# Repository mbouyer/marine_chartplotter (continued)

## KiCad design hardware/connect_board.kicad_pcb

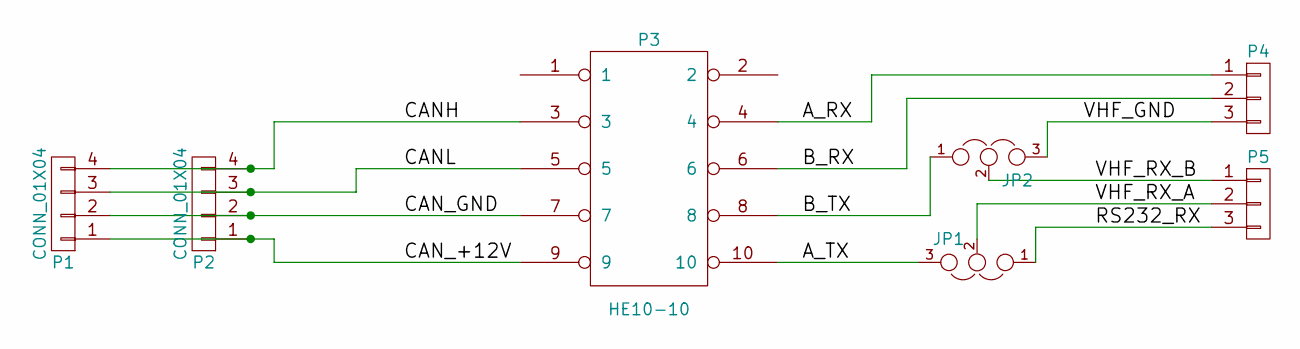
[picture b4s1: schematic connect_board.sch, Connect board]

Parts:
JP1, JP2: JUMPER3; Pin_Header_Straight_1x03
P1, P2: CONN_01X04; phoenix_1770979
P3: HE10-10; he10s-10d
P4, P5: CONN_01X03; TerminalBlock_Pheonix_MPT-2.54mm_3pol

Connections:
/A_RX: P3.4, P4.1
/A_TX: JP1.3, P3.10
/B_RX: P3.6, P4.2
/B_TX: JP2.1, P3.8
/CANH: P1.4, P2.4, P3.3
/CANL: P1.3, P2.3, P3.5
/CAN_+12V: P1.1, P2.1, P3.9
/CAN_GND: P1.2, P2.2, P3.7
/RS232_RX: JP1.1, P5.3
/VHF_GND: JP2.3, P4.3
/VHF_RX_A: JP1.2, P5.2
/VHF_RX_B: JP2.2, P5.1

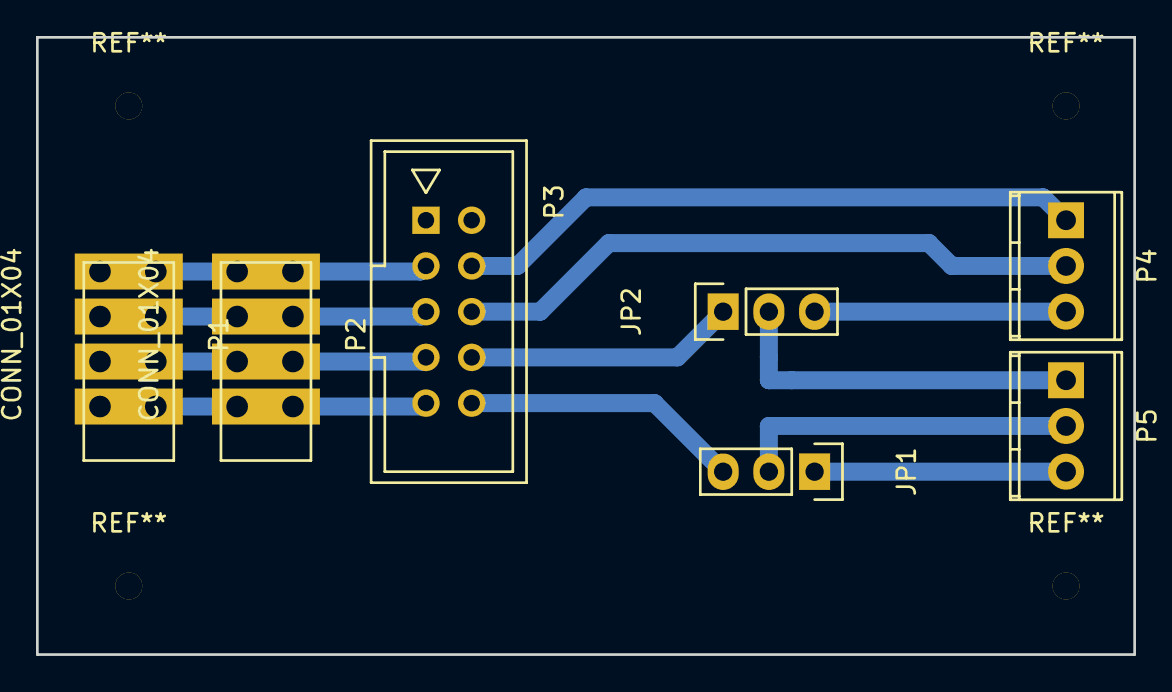
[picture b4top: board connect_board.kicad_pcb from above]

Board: 2 copper layers, 61.0 x 34.3 mm, 7 parts (0 on the bottom side), 12 nets.

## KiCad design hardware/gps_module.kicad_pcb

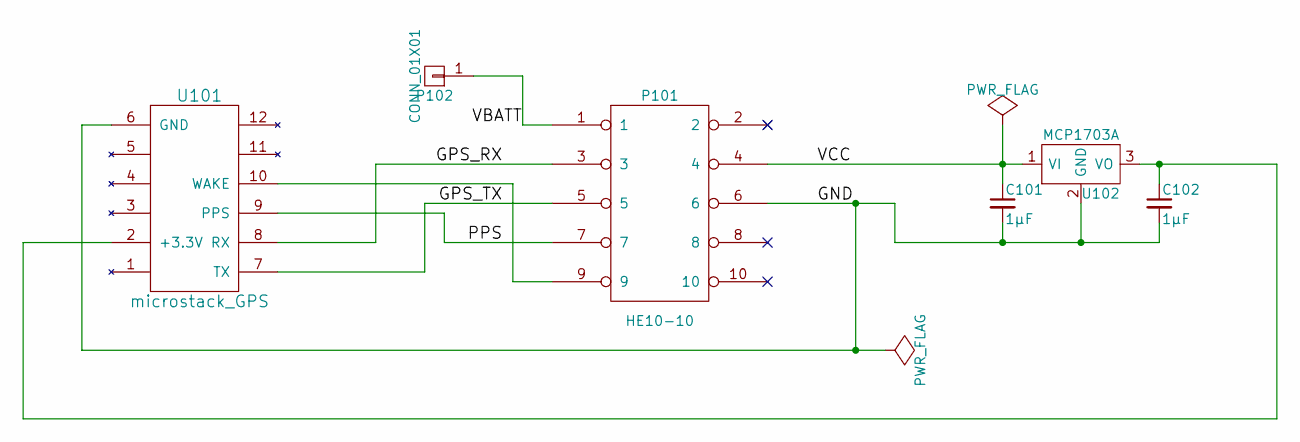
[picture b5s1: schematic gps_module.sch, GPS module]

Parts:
C101, C102: 1µF; C_0805_HandSoldering
P101: HE10-10; he10s-10d
P102: CONN_01X01; Pin_Header_Straight_1x01
U101: microstack_GPS; microstack
U102: MCP1703A; SOT-223-Tto2

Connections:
/GND: C101.2, C102.2, P101.6, U101.6 (GND), U102.2 (GND)
/GPS_RX: P101.3, U101.8 (RX)
/GPS_TX: P101.5, U101.7 (TX)
/PPS: P101.7, U101.9 (PPS)
/VBATT: P101.1, P102.1
/VCC: C101.1, P101.4, U102.1 (VI)
unnamed: C102.1, U101.2 (+3.3V), U102.3 (VO)
unnamed: P101.9, U101.10 (WAKE)

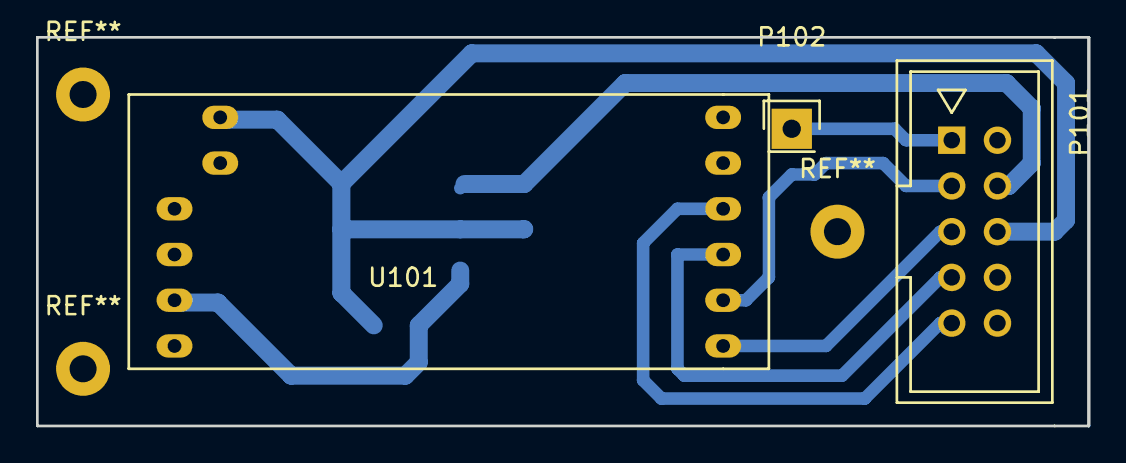
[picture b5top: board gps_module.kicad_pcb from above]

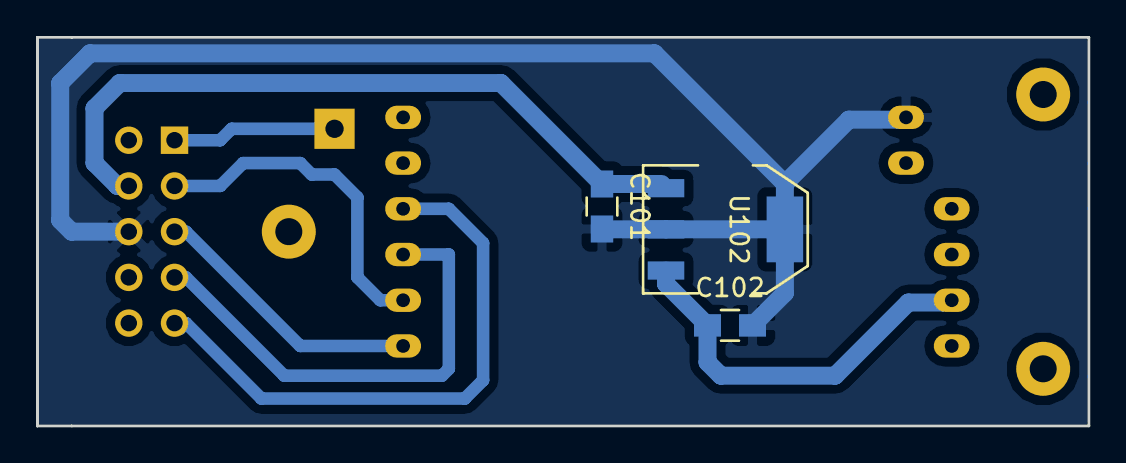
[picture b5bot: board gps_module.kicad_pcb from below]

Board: 2 copper layers, 58.4 x 21.6 mm, 6 parts (3 on the bottom side), 8 nets.

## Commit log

2016-03-13 Add a readme file
2016-03-15 Add a link to wiki
2016-03-17 Add hardware schematics and PCB
2016-03-18 Add metadata information to sheets Add pdf for the schematics
2016-03-19 Swap D and S of Q503 (oups)
2016-03-19 Rename machine_gps_can to marine_gps_can (typo)
2016-04-28 Add software-related bits: configuration, firmware for the pic18 and associated i2c driver for the NetBSD side.
2016-04-29 Add photos of the PCBs
2016-04-29 Smaller images
2016-05-30 Add a C program to switch the GPS module to 4800 bauds.
2016-09-08 Add an image of the product
2018-04-03 Add a interrupt bit in the status register interrupt also on key release event bump version
2018-04-03 Handle FDT-based config Because of the lack of mask/unmask in FDT kernels, switch to edge-triggered irq Use the interrupt bit in status request at last rev 0x11 for power button handling
2018-04-03 Switch to fdt-based SUNXI kernel. Add the associated dts config.
2019-01-11 Add new edisplay PCB module, an USB-connected external LCD display.
2019-03-15 Add design file for the front PMMA screen
2019-03-15 Fix mode
2019-06-25 Inital commit of external USB display software
2019-06-25 Style
2019-06-25 Cleanup display init
2019-06-26 SPI bug fixes and optimisations
2019-06-26 Redo input handlings
2019-06-26 Try to not discard events
2019-06-27 More DMA use use dual buffer for bulk input bump bulk size to the max (64)
2019-12-09 Move prevous code under demo/, and import lvgl-based interface, Handle some navigation data from canbus at this time (sill WIP). Handle only PC driver at this time.
2019-12-09 For output use LAT registers intead of PORT
2019-12-09 Add missing files from lvgl
2019-12-10 misc cleanups
2019-12-10 Remove stray files
2019-12-10 Restructure for upcoming USB edisplay drivers
2019-12-10 drivers for the USB edisplay. Untested.
2019-12-11 No need for driver includes here.
2019-12-11 Fix signed/unsigned issue really report buttons state, not just click events
2019-12-11 Some cleanups, helps with fast hosts. We may need interrupts for USB processing in the future.
2019-12-11 Cleanup displays and string descriptors
2019-12-11 Correct UC1610 initialisation Close and restart USB connection on any error; we don't get specific error when the device is disconnected On USB init send LV_EVENT_REFRESH to the top layer.
2019-12-12 Don't flood stderr when the USB device is disconnected. Fix NULL deref if the USB device is connected before app is started.
2019-12-12 Add a com_command structure for sending commands to the PIC. Implement backlight control, and switch LED control to PWM.
2019-12-12 Use pic/comms.h for commands sent to, and status from the PIC Implement backlight control. Dimm the LED when backlight it on
2020-02-02 Force software rendering for SDL2, to work around a bug on NetBSD/i386
2020-02-02 Work in progress on autopilot PGNs support.
2020-02-06 Add some qcad files from edisplay design
2020-02-06 Make pages handling more modular Split display functions in different files.
2020-02-06 Add defines for buttons
2020-02-06 print key value for LV_EVENT_KEY
2020-02-09 focus/unfocus individual pages instead of the top level object for encoder. Implement page button
2020-02-09 Fix page cycle handling Add empty callback for group focus/edit style, we don't want style changes on the page obj.
2020-02-13 work in progres on autopilot and control frames implementation
2020-02-13 Handle invalid heading from command unit
2020-02-13 private_command_engage_tx: handle invalid heading
2020-02-13 autopilot: implement start/stop
2020-02-13 Implement knob actions for autopilot
2020-02-13 Set the dst address of control frames per frame. Move dst address handling for autopilot frames to nmea2000_autopilot_tx
2020-02-13 pass cancel events as LV_KEY_ESC to focused obj. Handle cancel in light_action(). While there cleanup set but unused var.
2020-02-13 Kill wrong cast
2020-02-13 Implement cancel for page menu. Turn backlight on if needed when entering light slider.
2020-02-13 Fix autopilot heading display
2020-02-13 Add a mutex to protect lvgl from concurent calls.
2020-02-13 Center display
2020-02-13 Also display param slot
2020-02-15 Allow enc group to be empty. focus pages only if there is no focused object in the group.
2020-02-15 Factor out common code for transient objects in transient_open(). For symetry rename enc_group_close() to transcient_close().
2020-02-15 make transient_() global
2020-02-15 Factor out transient list creations. Add list selection of param slot for autopilot
2020-02-15 better aligneent for transient lists
2020-03-09 Adjust base depth Fix warning message
2020-03-14 Fix place of conges()
2020-03-21 Send change slot commands. Fix key handlings
2020-03-21 switch to event-based update system and get rid of display lock.
2020-03-21 We can't send event without mutex in multithreaded apps (sigh). So just write values to memory in the n2k rx thread, and update display in the main one.
2020-03-21 Implement requesting slot factors
2020-03-24 Allow more transient pages: add a epage_is_transient entry to edisp_page_t, and test this instead of handling only the epage_retro case. Add work in progress on pilot params edit
2020-03-26 Add a new widget, lv_eslider, derived from lv_slider, more usefull for rotating knobs. It display its value in text, doesn't show the knob, and allows different step values.
2020-03-28 Allow editing PID factors
2020-03-28 When autopilot is in standby, switch to off on cancel event.
2020-04-05 Handle remote display events
2020-04-06 Display and handle command errors
2020-04-13 Put lv_eslider.c in the right place
2020-04-26 When a route is activated, or we switch to a new waypoint, switch to the navigation page.
2022-05-28 Adjust lv_gauge for wind direction gauge
2022-05-28 Add a wind data page, with direction gauge. Todo: collect data and compute tws/twa and vmg.
2022-05-28 Use large text for VMG, adjust positions.
2022-05-29 Receive and display apparent wind data Copy heading from autopilot page to winddata
2022-05-29 Complete compute/display of true wind and vmg.
2022-05-29 Fix display of small negative VMG
2022-05-30 Redo computations with vectors, we can't just average angles this way.
2022-05-31 Need to use b_cog no cog to compute true wind
